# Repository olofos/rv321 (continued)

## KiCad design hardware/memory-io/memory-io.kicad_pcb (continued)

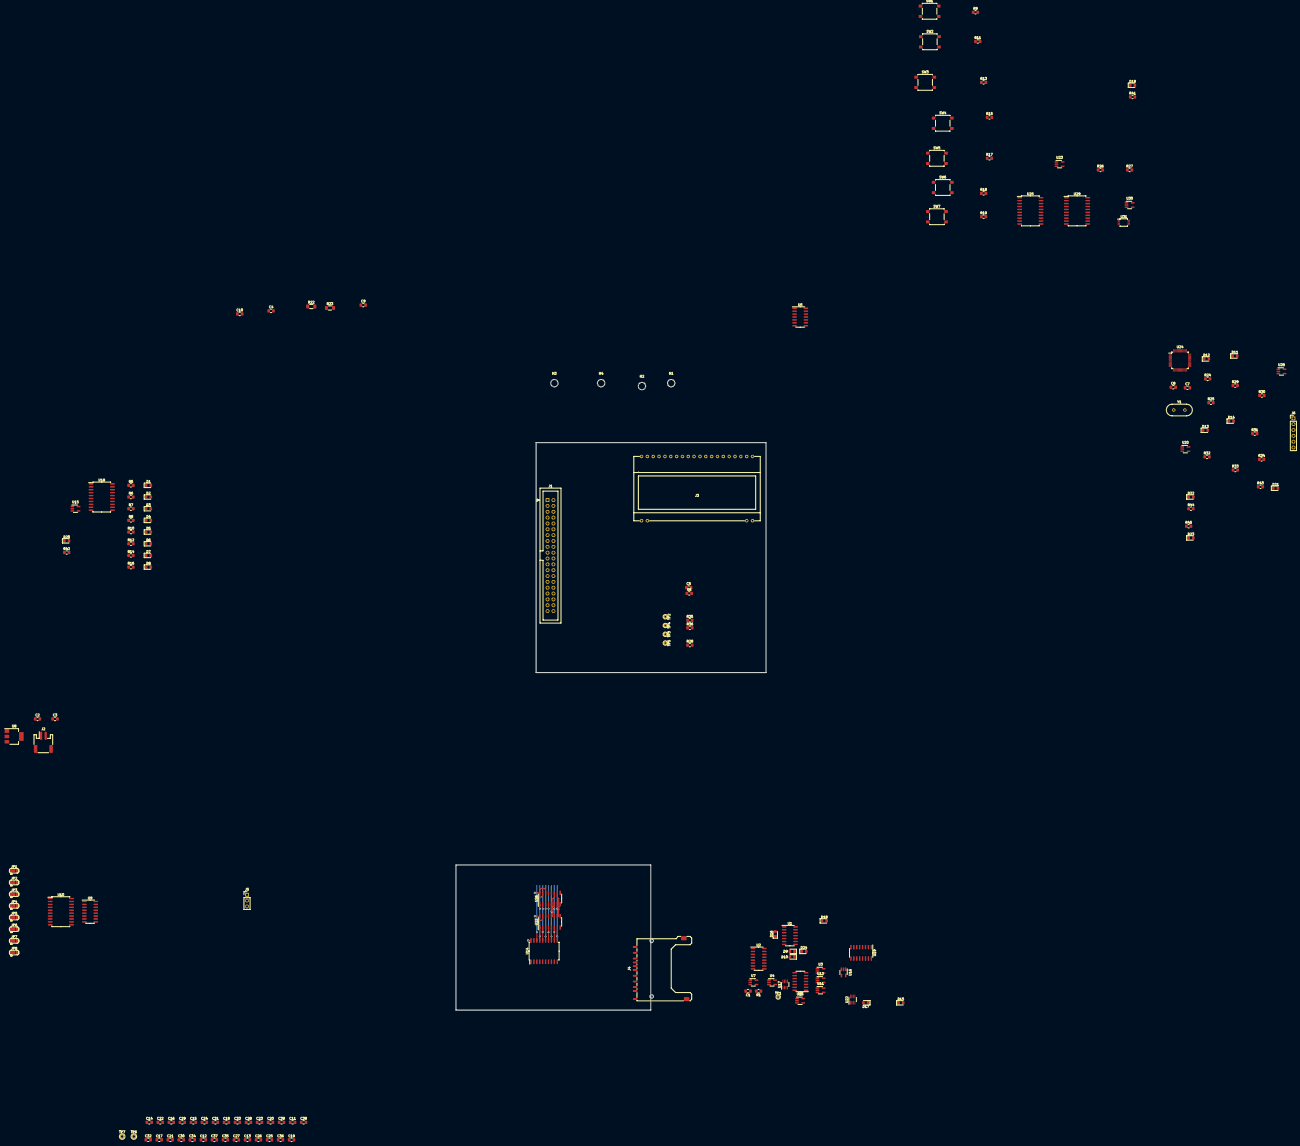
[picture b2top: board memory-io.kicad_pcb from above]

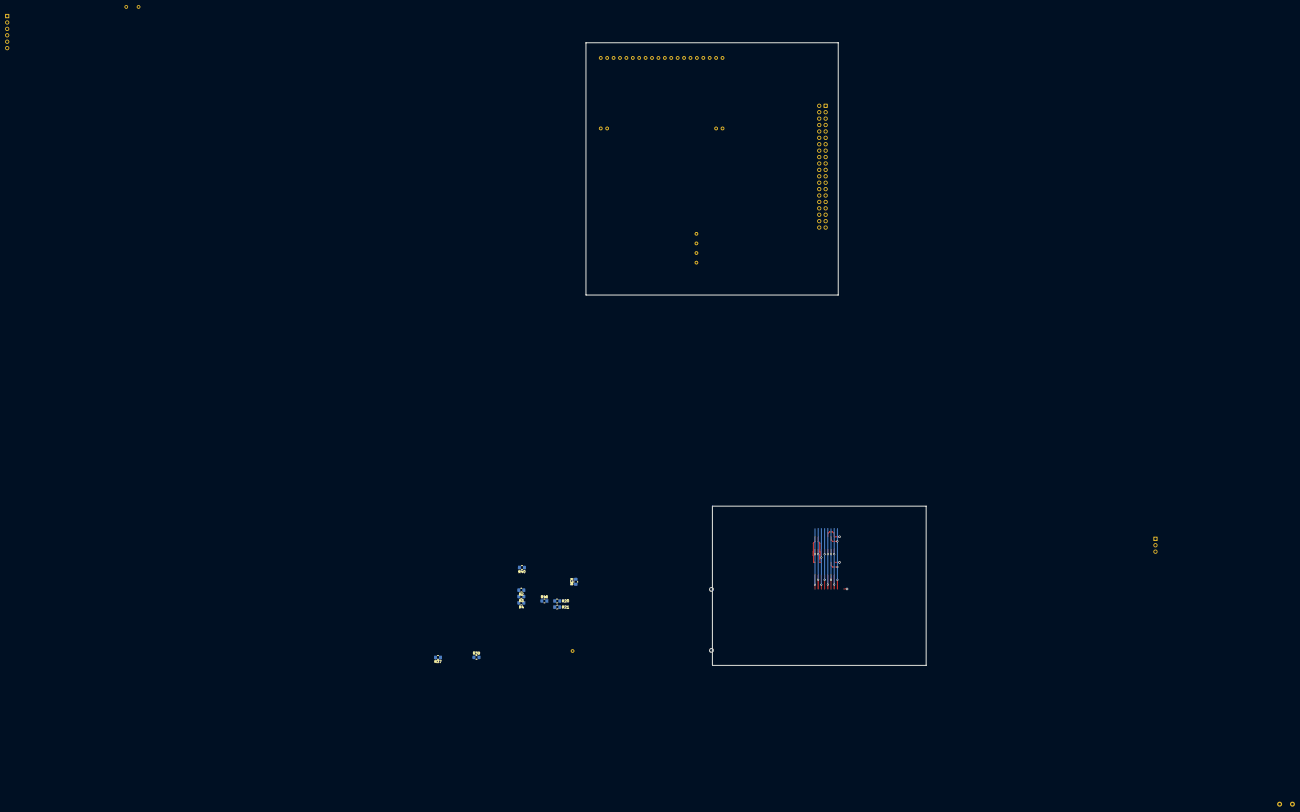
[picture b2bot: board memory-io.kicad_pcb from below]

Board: 4 copper layers, 172 parts (10 on the bottom side), 140 nets.

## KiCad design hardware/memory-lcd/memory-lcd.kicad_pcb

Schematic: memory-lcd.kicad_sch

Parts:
C1, C2: 1u; C_0805_2012Metric_Pad1.15x1.40mm_HandSolder
C3, C4, C5: 100n; C_0805_2012Metric_Pad1.15x1.40mm_HandSolder
H1, H2, H3, H4: MountingHole; MountingHole_3.2mm_M3
J1: NHD-0220FZ
J2: Conn_Mem_Ext; IDC-Header_2x20_P2.54mm_Vertical
J3: Conn_Power; JST_PH_S2B-PH-SM4-TB_1x02-1MP_P2.00mm_Horizontal
JP1, JP2, JP3, JP4, JP5, JP6: SolderJumper_3_Bridged12; SolderJumper-3_P1.3mm_Bridged2Bar12_RoundedPad1.0x1.5mm
RV1: 10k; Potentiometer_Bourns_3386P_Vertical
U1: 74HC688; SO-20_12.8x7.5mm_P1.27mm
U2: 74LVC1G08; SOT-23-5_HandSoldering
U3: MIC5504-3.3YM5; SOT-23-5_HandSoldering
U4: 74LVC1G04; SOT-23-5_HandSoldering

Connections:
/A0: J1.4 (RS), J2.2 (A0)
/A1: J2.3 (A1), U1.6 (P2)
/A2: J2.4 (A2), U1.8 (P3)
/A3: J2.5 (A3), U1.11 (P4)
/A4: J2.6 (A4), U1.13 (P5)
/A5: J2.7 (A5), U1.15 (P6)
/A6: J2.8 (A6), U1.17 (P7)
/A7: J2.9 (A7)
/A8: J2.10 (A8)
/A9: J2.11 (A9)
/A10: J2.12 (A10)
/A11: J2.13 (A11)
/A12: J2.14 (A12)
/A13: J2.15 (A13)
/A14: J2.16 (A14)
/A15: J2.17 (A15)
/A16: J2.18 (A16)
/A17: J2.19 (A17)
/A18: J2.20 (A18)
/A19: J2.21 (A19)
/A20: J2.22 (A20)
/A21: J2.23 (A21)
/A22: J2.24 (A22)
/A23: J2.25 (A23)
/A30: J2.26 (A30), U1.2 (P0)
/A31: J2.27 (A31), U1.4 (P1)
/B1: JP1.2 (C), U1.7 (R2)
/B2: JP2.2 (C), U1.9 (R3)
/B3: JP3.2 (C), U1.12 (R4)
/B4: JP4.2 (C), U1.14 (R5)
/B5: JP5.2 (C), U1.16 (R6)
/B6: JP6.2 (C), U1.18 (R7)
/D0: J1.14 (DB7), J2.32 (D0)
/D1: J1.13 (DB6), J2.33 (D1)
/D2: J1.12 (DB5), J2.34 (D2)
/D3: J1.11 (DB4), J2.35 (D3)
/D4: J1.10 (DB3), J2.36 (D4)
/D5: J1.9 (DB2), J2.37 (D5)
/D6: J1.8 (DB1), J2.38 (D6)
/D7: J1.7 (DB0), J2.39 (D7)
/LCD_E: J1.6 (E), U4.4
/V_IN: C1.2, J3.1 (VCC), U3.1 (VIN), U3.3 (EN)
/~LCD_E: U1.19 (P=R), U4.2
/~MEM_E: U1.1 (G), U2.4
/~MEM_OE: J2.30 (~MEM_OE), U2.1
/~MEM_WE: J1.5 (R/~W), J2.31 (~MEM_WE), U2.2
/~RESET: J2.28 (~RESET)
/~WAIT: J2.29 (~WAIT)
GND: C1.1, C2.1, C3.1, C4.1, C5.1, J1.1 (GND), J1.16 (K-), J2.1 (GND), J2.40 (GND), J3.2 (GND), J3.MP, JP1.1 (A), JP2.1 (A), JP3.1 (A), JP4.1 (A), JP5.1 (A), JP6.1 (A), RV1.3, U1.5 (R1), U1.10 (GND), U2.3 (GND), U3.2 (GND), U4.3 (GND)
unnamed: J1.3 (Vcontr), RV1.2
VCC: C2.2, C3.2, C4.2, C5.2, J1.2 (VCC), J1.15 (A+), JP1.3 (B), JP2.3 (B), JP3.3 (B), JP4.3 (B), JP5.3 (B), JP6.3 (B), RV1.1, U1.3 (R0), U1.20 (VCC), U2.5 (VCC), U3.5 (VOUT), U4.5 (VCC)

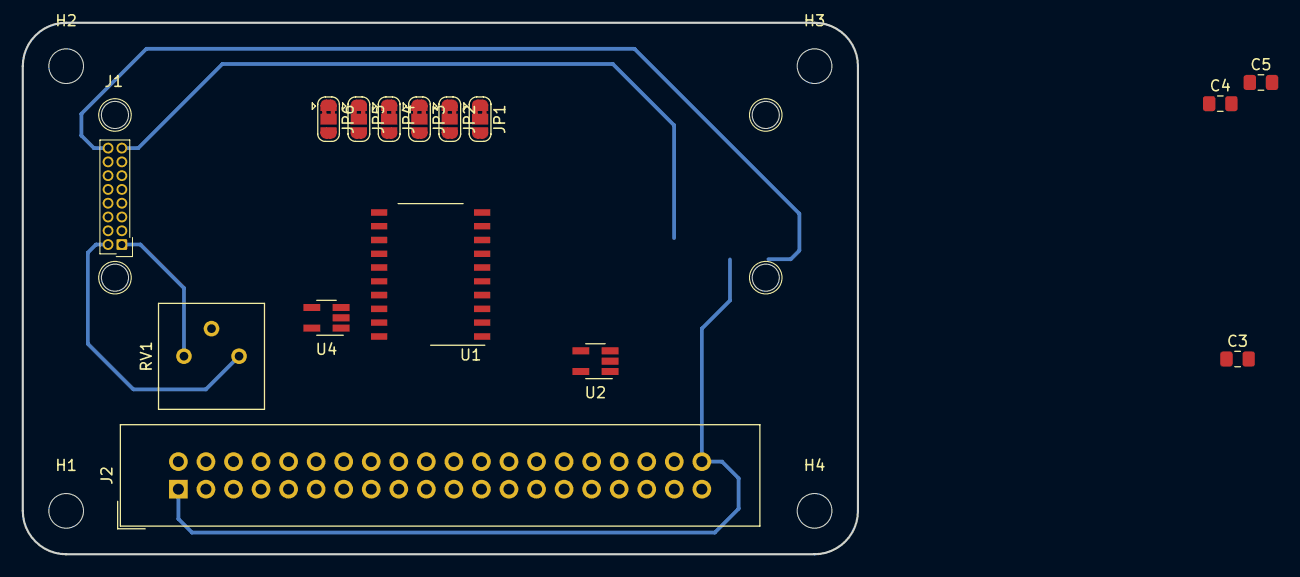
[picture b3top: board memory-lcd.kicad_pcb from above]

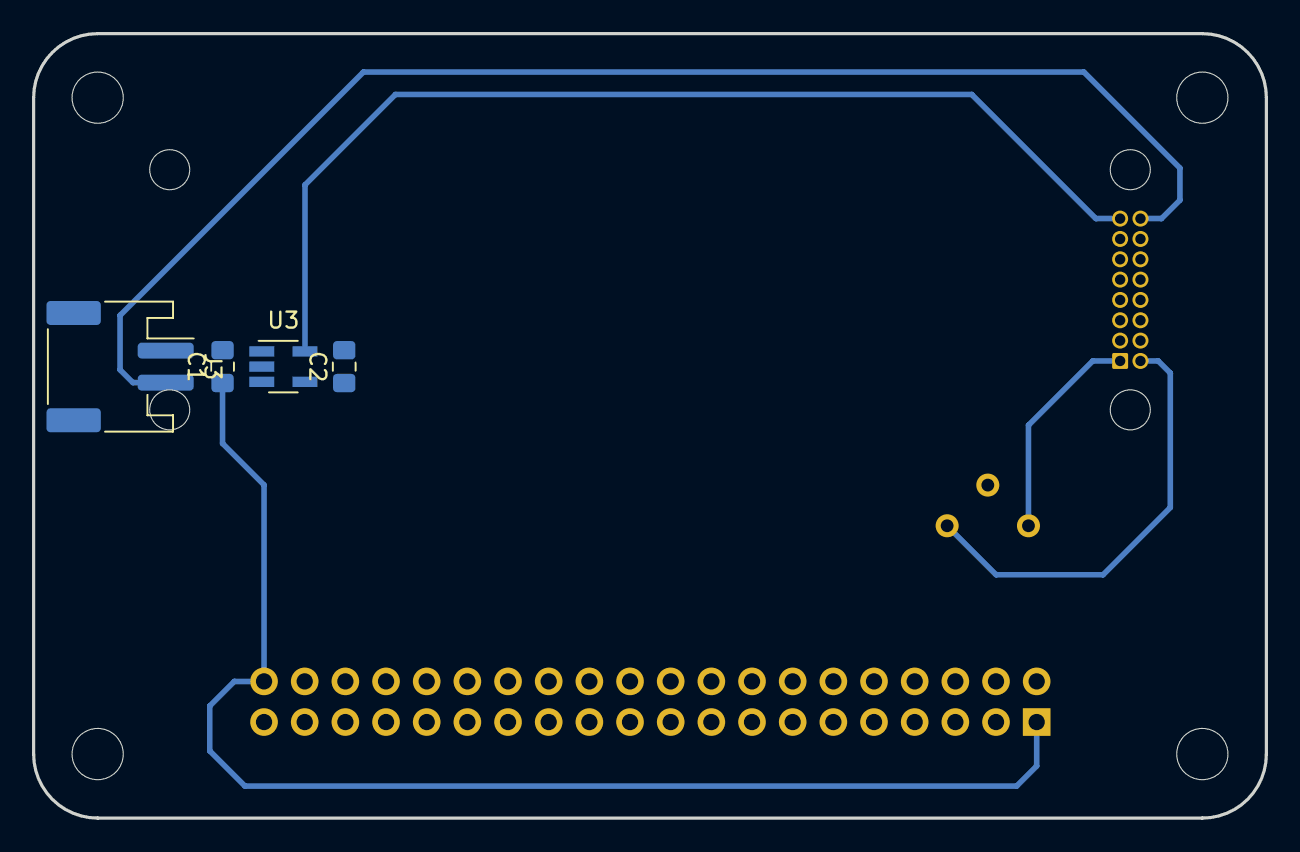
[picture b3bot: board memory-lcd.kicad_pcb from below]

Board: 2 copper layers, 77.0 x 49.0 mm, 23 parts (4 on the bottom side), 32 nets.

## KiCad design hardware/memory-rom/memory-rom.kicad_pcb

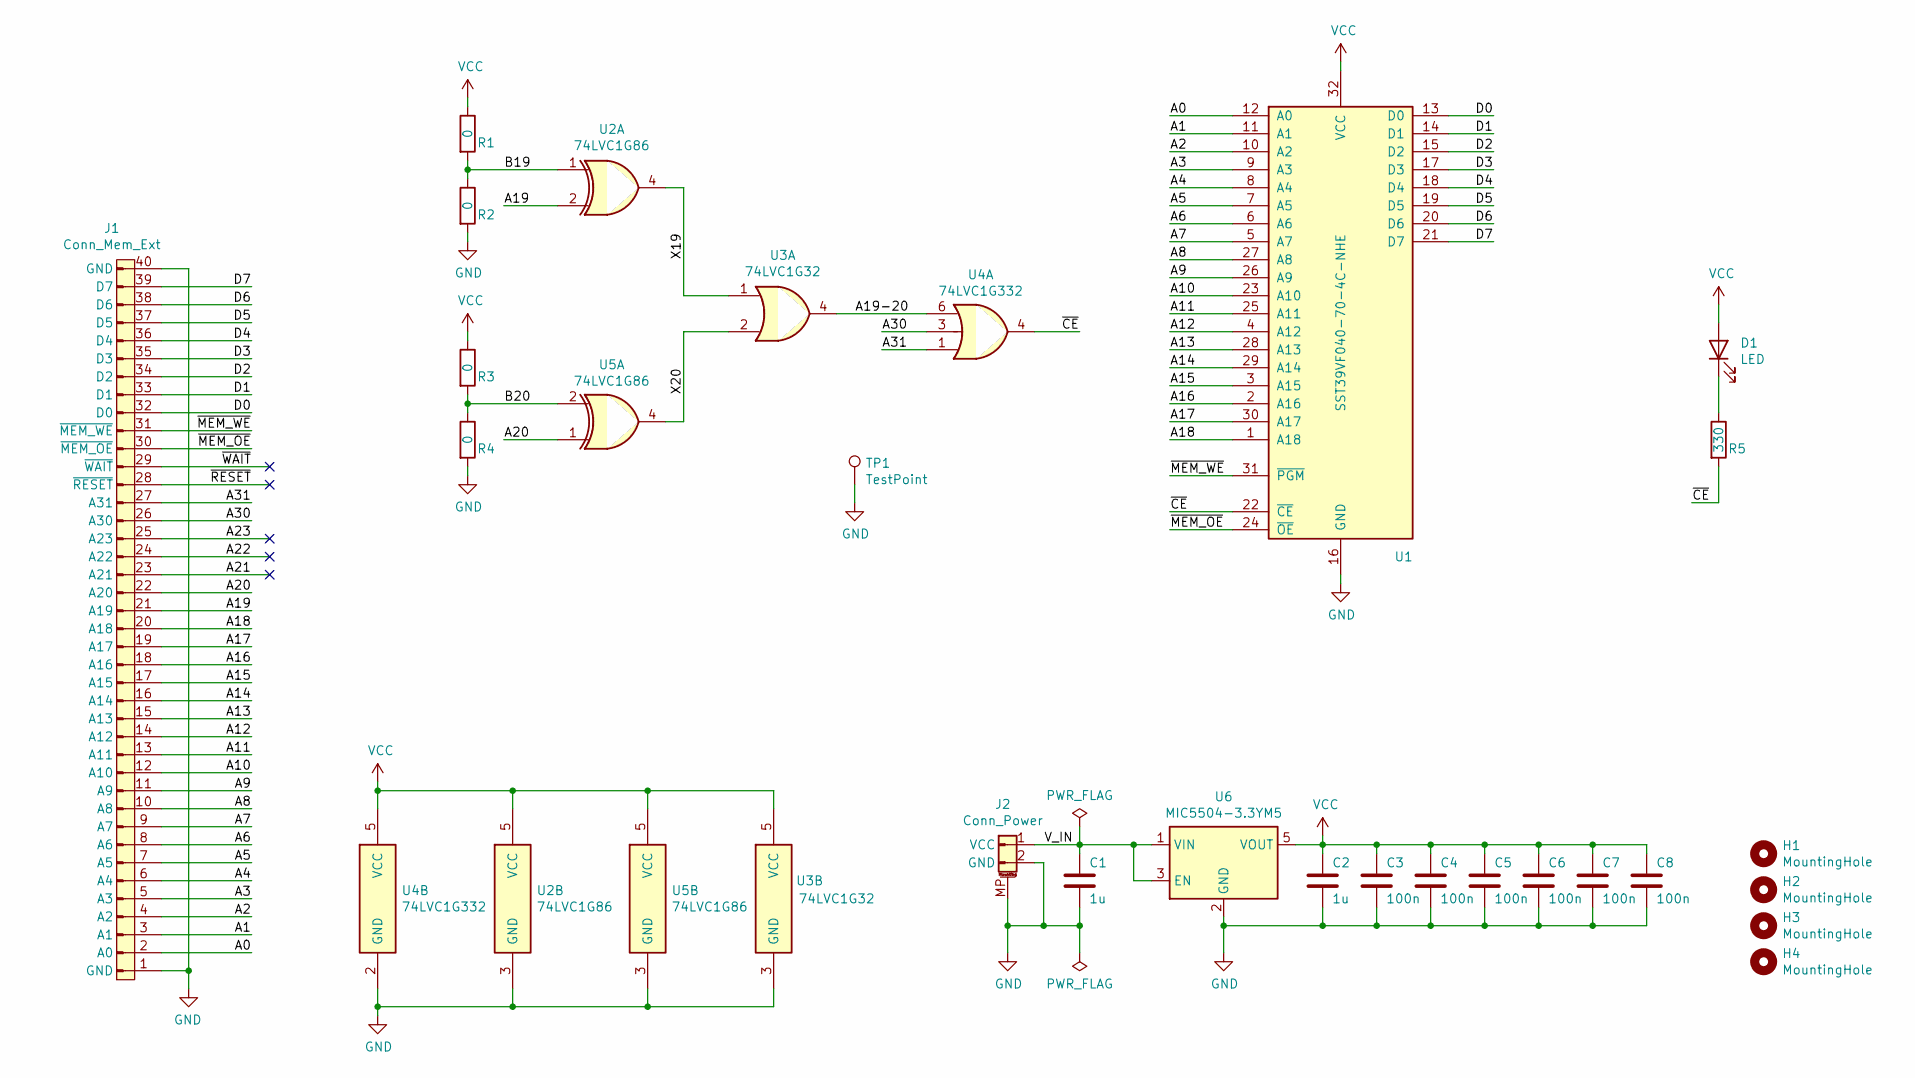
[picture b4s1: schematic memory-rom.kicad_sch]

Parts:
C1, C2: 1u; C_0805_2012Metric_Pad1.15x1.40mm_HandSolder
C3, C4, C5, C6, C7, C8: 100n; C_0805_2012Metric_Pad1.15x1.40mm_HandSolder
D1: LED; LED_0805_2012Metric_Pad1.15x1.40mm_HandSolder
H1, H2, H3, H4: MountingHole; MountingHole_3.2mm_M3
J1: Conn_Mem_Ext; IDC-Header_2x20_P2.54mm_Vertical
J2: Conn_Power; JST_PH_S2B-PH-SM4-TB_1x02-1MP_P2.00mm_Horizontal
R1, R2, R3, R4: 0; R_0805_2012Metric_Pad1.15x1.40mm_HandSolder
R5: 330; R_0805_2012Metric_Pad1.15x1.40mm_HandSolder
TP1: TestPoint; TestPoint_THTPad_D2.0mm_Drill1.0mm
U1: SST39VF040-70-4C-NHE; PLCC-32-socket-2M-8432-11B1-RK-TP
U2, U5: 74LVC1G86; SOT-23-5_HandSoldering
U3: 74LVC1G32; SOT-23-5_HandSoldering
U4: 74LVC1G332; SOT-23-6_Handsoldering
U6: MIC5504-3.3YM5; SOT-23-5_HandSoldering

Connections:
/A0: J1.2 (A0), U1.12 (A0)
/A1: J1.3 (A1), U1.11 (A1)
/A2: J1.4 (A2), U1.10 (A2)
/A3: J1.5 (A3), U1.9 (A3)
/A4: J1.6 (A4), U1.8 (A4)
/A5: J1.7 (A5), U1.7 (A5)
/A6: J1.8 (A6), U1.6 (A6)
/A7: J1.9 (A7), U1.5 (A7)
/A8: J1.10 (A8), U1.27 (A8)
/A9: J1.11 (A9), U1.26 (A9)
/A10: J1.12 (A10), U1.23 (A10)
/A11: J1.13 (A11), U1.25 (A11)
/A12: J1.14 (A12), U1.4 (A12)
/A13: J1.15 (A13), U1.28 (A13)
/A14: J1.16 (A14), U1.29 (A14)
/A15: J1.17 (A15), U1.3 (A15)
/A16: J1.18 (A16), U1.2 (A16)
/A17: J1.19 (A17), U1.30 (A17)
/A18: J1.20 (A18), U1.1 (A18)
/A19: J1.21 (A19), U2.2
/A19-20: U3.4, U4.6
/A20: J1.22 (A20), U5.1
/A21: J1.23 (A21)
/A22: J1.24 (A22)
/A23: J1.25 (A23)
/A30: J1.26 (A30), U4.3
/A31: J1.27 (A31), U4.1
/B19: R1.2, R2.1, U2.1
/B20: R3.2, R4.1, U5.2
/D0: J1.32 (D0), U1.13 (D0)
/D1: J1.33 (D1), U1.14 (D1)
/D2: J1.34 (D2), U1.15 (D2)
/D3: J1.35 (D3), U1.17 (D3)
/D4: J1.36 (D4), U1.18 (D4)
/D5: J1.37 (D5), U1.19 (D5)
/D6: J1.38 (D6), U1.20 (D6)
/D7: J1.39 (D7), U1.21 (D7)
/V_IN: C1.2, J2.1 (VCC), U6.1 (VIN), U6.3 (EN)
/X19: U2.4, U3.1
/X20: U3.2, U5.4
/~CE: R5.2, U1.22 (~CE), U4.4
/~MEM_OE: J1.30 (~MEM_OE), U1.24 (~OE)
/~MEM_WE: J1.31 (~MEM_WE), U1.31 (~PGM)
/~RESET: J1.28 (~RESET)
/~WAIT: J1.29 (~WAIT)
GND: C1.1, C2.1, C3.1, C4.1, C5.1, C6.1, C7.1, C8.1, J1.1 (GND), J1.40 (GND), J2.2 (GND), J2.MP, R2.2, R4.2, TP1.1, U1.16 (GND), U2.3 (GND), U3.3 (GND), U4.2 (GND), U5.3 (GND), U6.2 (GND)
unnamed: D1.1 (K), R5.1
VCC: C2.2, C3.2, C4.2, C5.2, C6.2, C7.2, C8.2, D1.2 (A), R1.1, R3.1, U1.32 (VCC), U2.5 (VCC), U3.5 (VCC), U4.5 (VCC), U5.5 (VCC), U6.5 (VOUT)

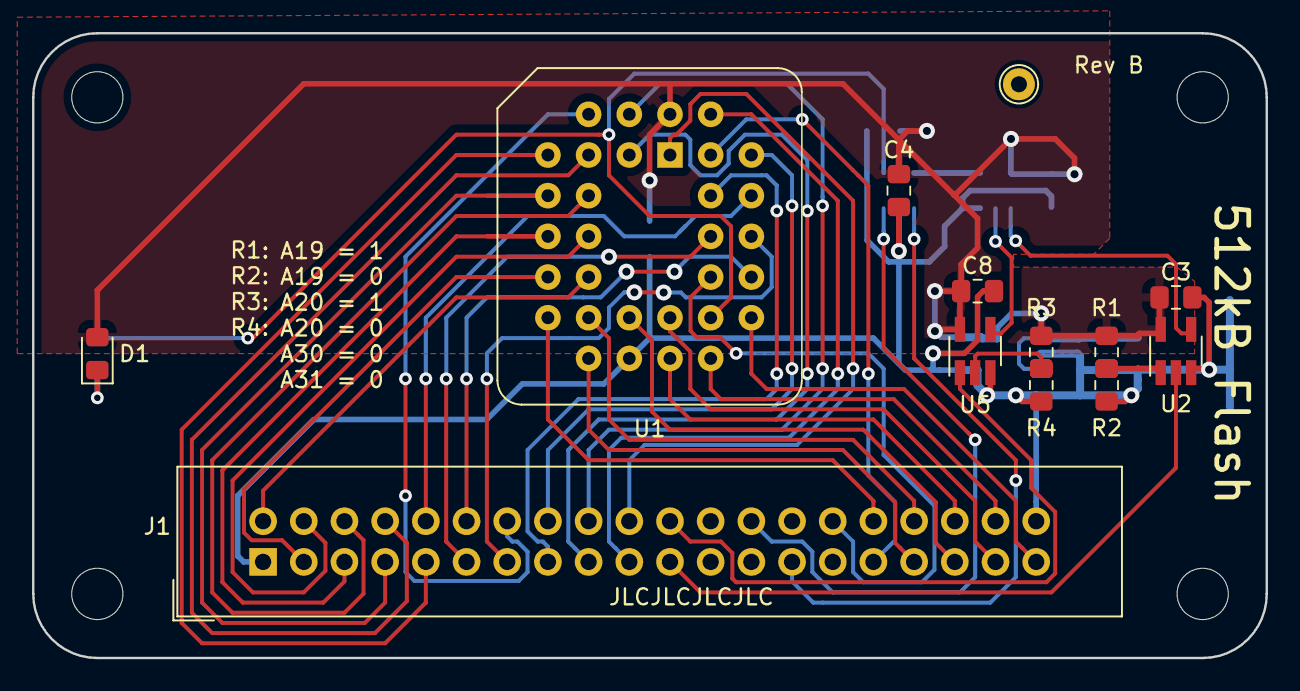
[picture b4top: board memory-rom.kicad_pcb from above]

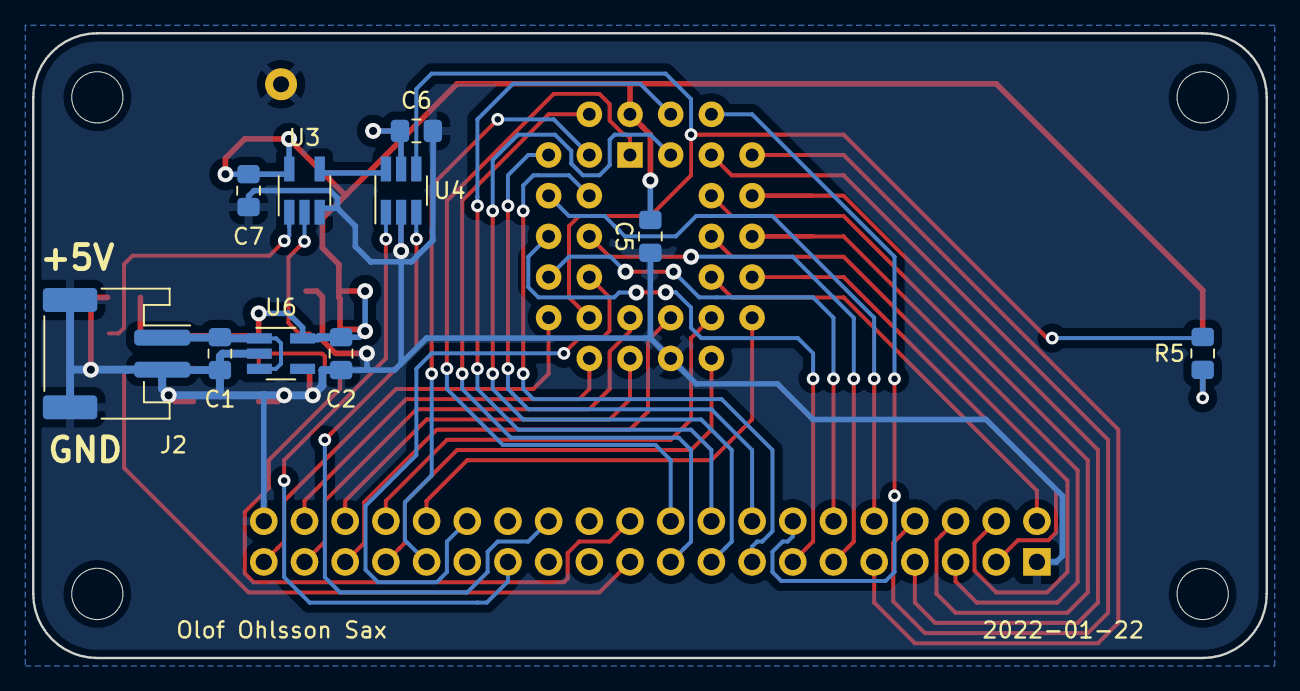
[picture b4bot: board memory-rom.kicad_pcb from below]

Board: 2 copper layers, 77.0 x 39.0 mm, 27 parts (10 on the bottom side), 43 nets.

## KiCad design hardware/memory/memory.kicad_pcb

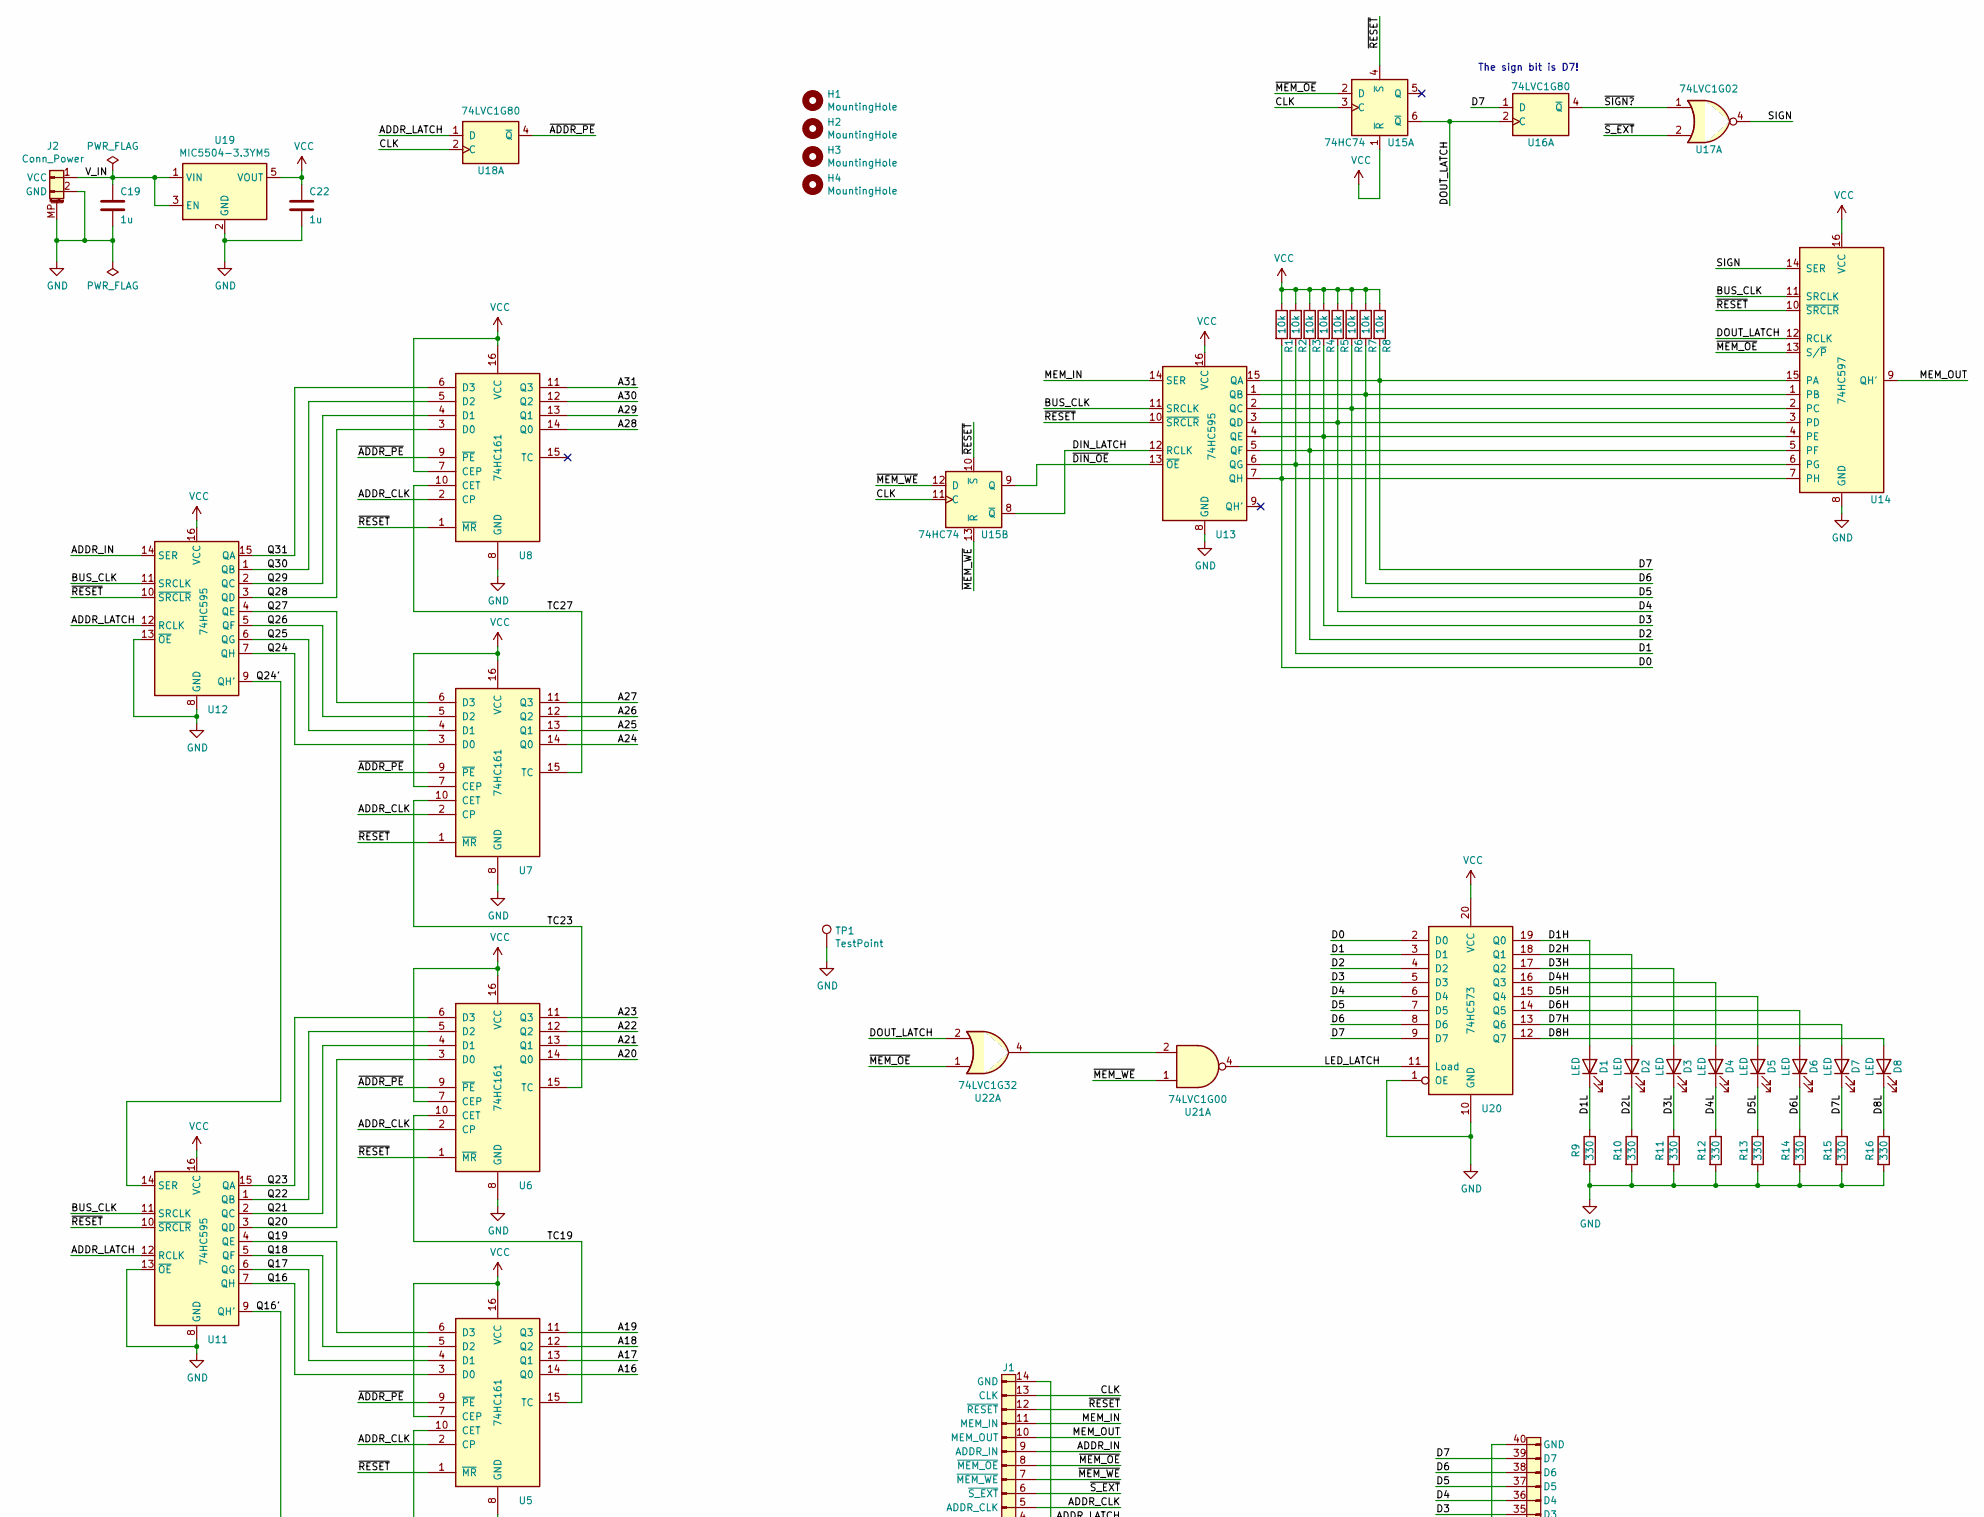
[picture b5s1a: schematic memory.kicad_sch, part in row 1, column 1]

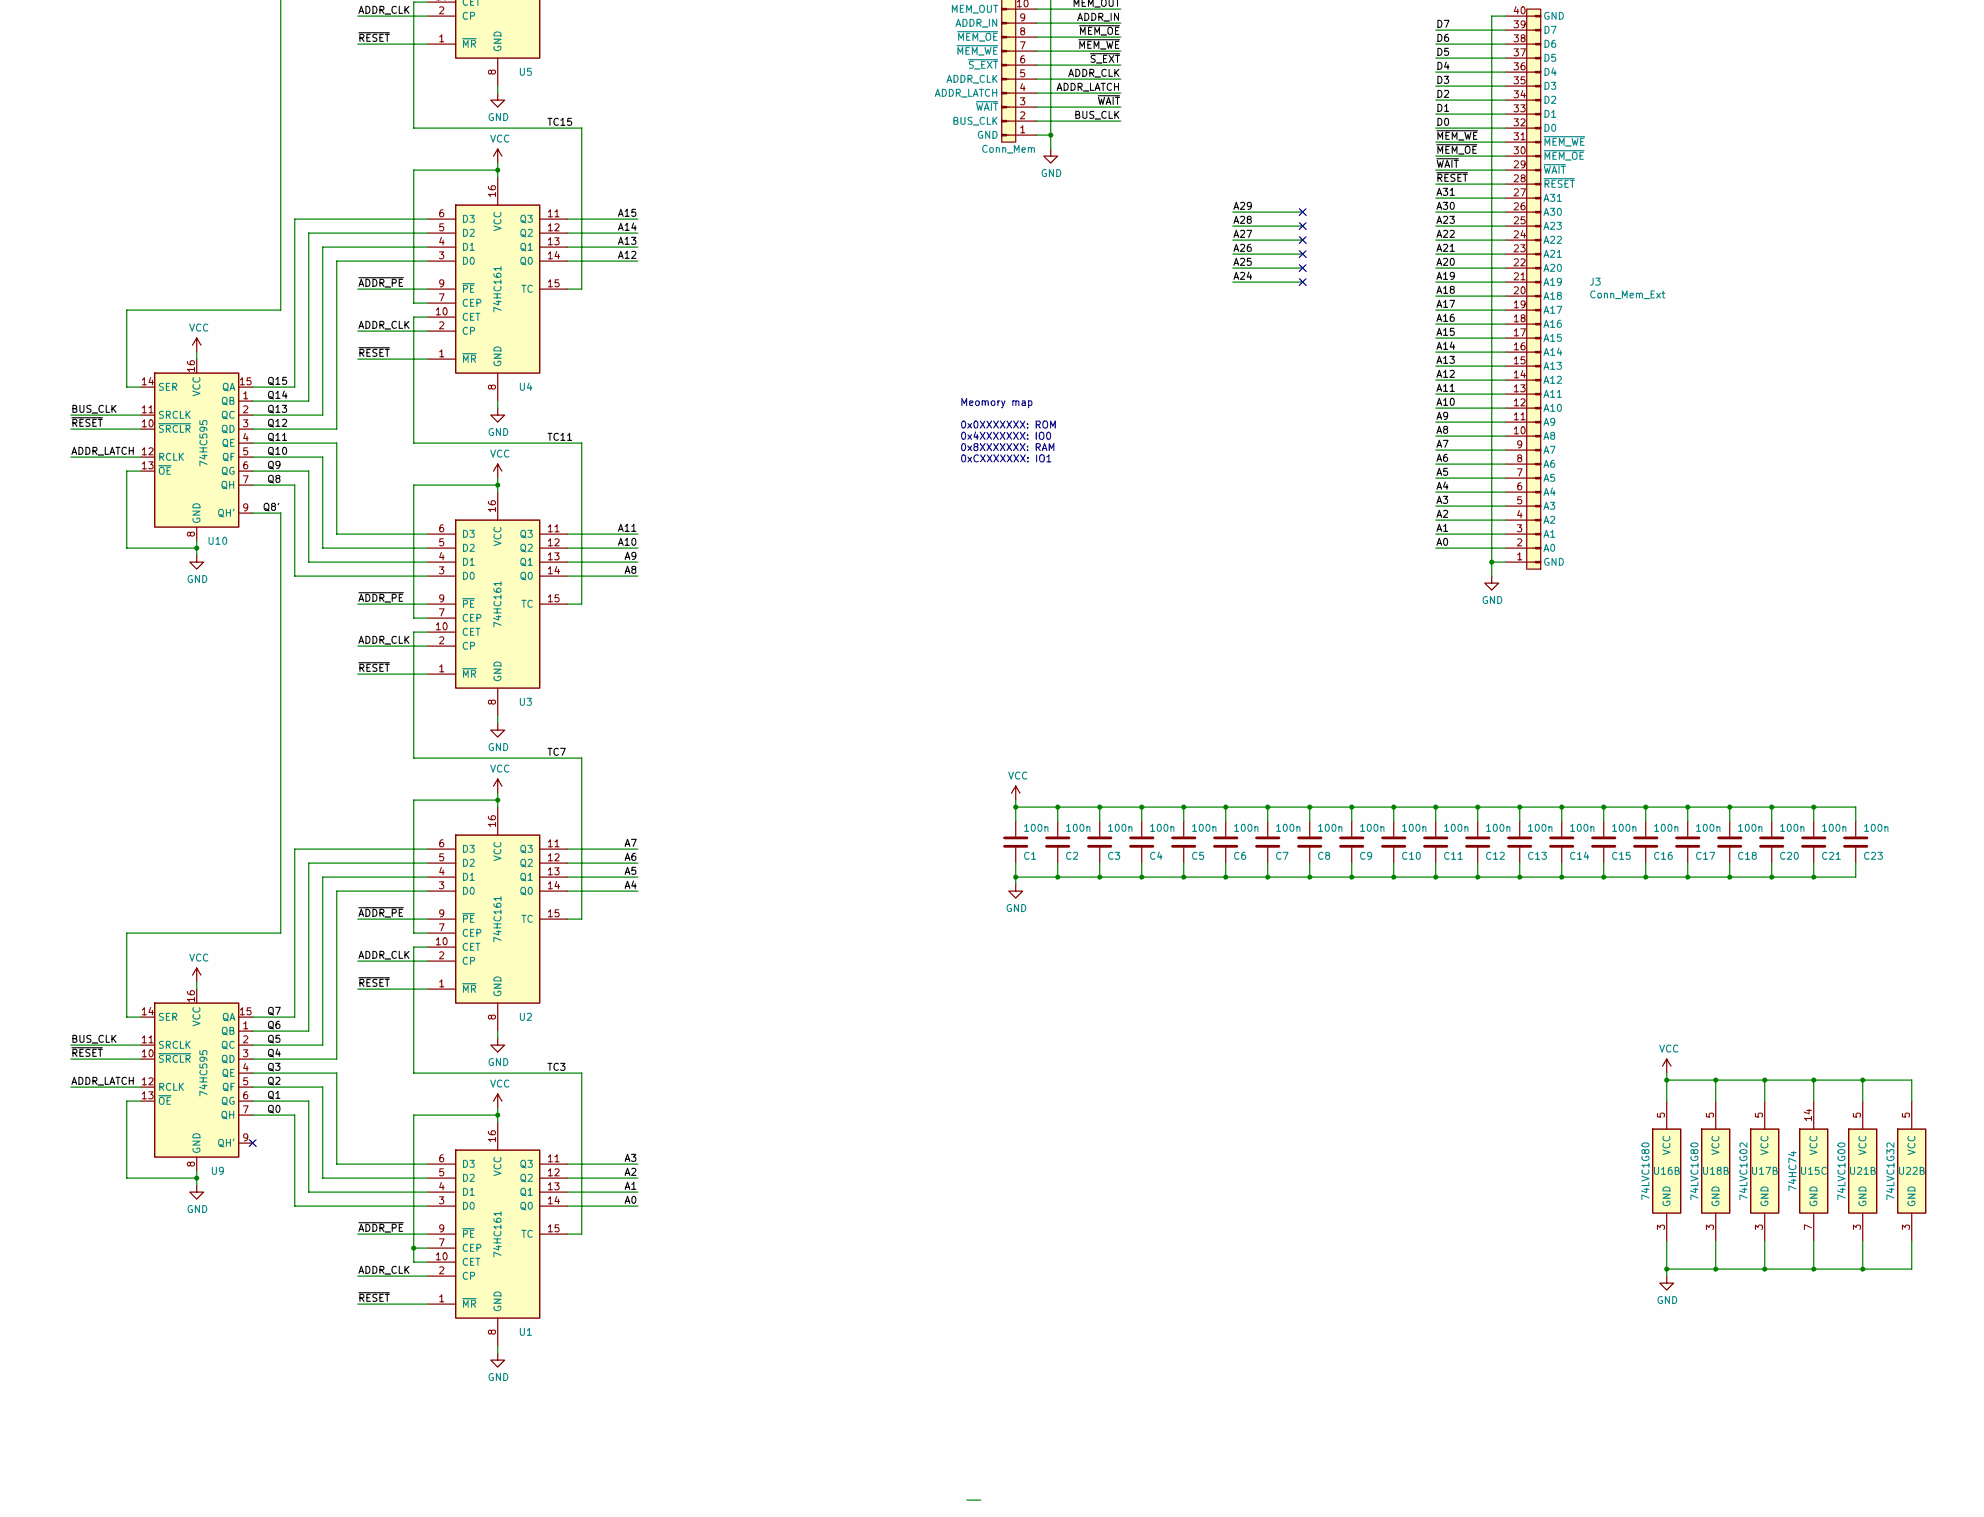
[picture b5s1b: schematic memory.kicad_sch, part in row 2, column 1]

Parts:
C1, C2, C3, C4, C5, C6, C7, C8, C9, C10, C11, C12, C13, C14, C15, C16, C17, C18, C20, C21: 100n; C_0805_2012Metric_Pad1.15x1.40mm_HandSolder
C19, C22: 1u; C_0805_2012Metric_Pad1.15x1.40mm_HandSolder
C23: 100n; C_0805_2012Metric_Pad1.18x1.45mm_HandSolder
D1, D2, D3, D4, D5, D6, D7, D8: LED; LED_0805_2012Metric_Pad1.15x1.40mm_HandSolder
H1, H2, H3, H4: MountingHole; MountingHole_3.2mm_M3
J1: Conn_Mem; IDC-Header_2x07_P2.54mm_Vertical
J2: Conn_Power; JST_PH_S2B-PH-SM4-TB_1x02-1MP_P2.00mm_Horizontal
J3: Conn_Mem_Ext; IDC-Header_2x20_P2.54mm_Vertical
R1, R2, R3, R4, R5, R6, R7, R8: 10k; R_0805_2012Metric_Pad1.15x1.40mm_HandSolder
R9, R10, R11, R12, R13, R14, R15, R16: 330; R_0805_2012Metric_Pad1.15x1.40mm_HandSolder
TP1: TestPoint; TestPoint_THTPad_D2.0mm_Drill1.0mm
U1, U2, U3, U4, U5, U6, U7, U8: 74HC161; SOIC-16_3.9x9.9mm_P1.27mm
U9, U10, U11, U12, U13: 74HC595; SOIC-16_3.9x9.9mm_P1.27mm
U14: 74HC597; SOIC-16_3.9x9.9mm_P1.27mm
U15: 74HC74; SOIC-14_3.9x8.7mm_P1.27mm
U16, U18: 74LVC1G80; SOT-23-5_HandSoldering
U17: 74LVC1G02; SOT-23-5_HandSoldering
U19: MIC5504-3.3YM5; SOT-23-5_HandSoldering
U20: 74HC573; TSSOP-20_4.4x6.5mm_P0.65mm
U21: 74LVC1G00; SOT-23-5_HandSoldering
U22: 74LVC1G32; SOT-23-5_HandSoldering

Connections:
/A0: J3.2 (A0), U1.14 (Q0)
/A1: J3.3 (A1), U1.13 (Q1)
/A2: J3.4 (A2), U1.12 (Q2)
/A3: J3.5 (A3), U1.11 (Q3)
/A4: J3.6 (A4), U2.14 (Q0)
/A5: J3.7 (A5), U2.13 (Q1)
/A6: J3.8 (A6), U2.12 (Q2)
/A7: J3.9 (A7), U2.11 (Q3)
/A8: J3.10 (A8), U3.14 (Q0)
/A9: J3.11 (A9), U3.13 (Q1)
/A10: J3.12 (A10), U3.12 (Q2)
/A11: J3.13 (A11), U3.11 (Q3)
/A12: J3.14 (A12), U4.14 (Q0)
/A13: J3.15 (A13), U4.13 (Q1)
/A14: J3.16 (A14), U4.12 (Q2)
/A15: J3.17 (A15), U4.11 (Q3)
/A16: J3.18 (A16), U5.14 (Q0)
/A17: J3.19 (A17), U5.13 (Q1)
/A18: J3.20 (A18), U5.12 (Q2)
/A19: J3.21 (A19), U5.11 (Q3)
/A20: J3.22 (A20), U6.14 (Q0)
/A21: J3.23 (A21), U6.13 (Q1)
/A22: J3.24 (A22), U6.12 (Q2)
/A23: J3.25 (A23), U6.11 (Q3)
/A24: U7.14 (Q0)
/A25: U7.13 (Q1)
/A26: U7.12 (Q2)
/A27: U7.11 (Q3)
/A28: U8.14 (Q0)
/A29: U8.13 (Q1)
/A30: J3.26 (A30), U8.12 (Q2)
/A31: J3.27 (A31), U8.11 (Q3)
/ADDR_CLK: J1.5 (ADDR_CLK), U1.2 (CP), U2.2 (CP), U3.2 (CP), U4.2 (CP), U5.2 (CP), U6.2 (CP), U7.2 (CP), U8.2 (CP)
/ADDR_IN: J1.9 (ADDR_IN), U12.14 (SER)
/ADDR_LATCH: J1.4 (ADDR_LATCH), U9.12 (RCLK), U10.12 (RCLK), U11.12 (RCLK), U12.12 (RCLK), U18.1 (D)
/BUS_CLK: J1.2 (BUS_CLK), U9.11 (SRCLK), U10.11 (SRCLK), U11.11 (SRCLK), U12.11 (SRCLK), U13.11 (SRCLK), U14.11 (SRCLK)
/CLK: J1.13 (CLK), U15.3 (C), U15.11 (C), U18.2 (C)
/D0: J3.32 (D0), R1.2, U13.7 (QH), U14.7 (PH), U20.2 (D0)
/D1: J3.33 (D1), R2.2, U13.6 (QG), U14.6 (PG), U20.3 (D1)
/D1H: D1.2 (A), U20.19 (Q0)
/D1L: D1.1 (K), R9.1
/D2: J3.34 (D2), R3.2, U13.5 (QF), U14.5 (PF), U20.4 (D2)
/D2H: D2.2 (A), U20.18 (Q1)
/D2L: D2.1 (K), R10.1
/D3: J3.35 (D3), R4.2, U13.4 (QE), U14.4 (PE), U20.5 (D3)
/D3H: D3.2 (A), U20.17 (Q2)
/D3L: D3.1 (K), R11.1
/D4: J3.36 (D4), R5.2, U13.3 (QD), U14.3 (PD), U20.6 (D4)
/D4H: D4.2 (A), U20.16 (Q3)
/D4L: D4.1 (K), R12.1
/D5: J3.37 (D5), R6.2, U13.2 (QC), U14.2 (PC), U20.7 (D5)
/D5H: D5.2 (A), U20.15 (Q4)
/D5L: D5.1 (K), R13.1
/D6: J3.38 (D6), R7.2, U13.1 (QB), U14.1 (PB), U20.8 (D6)
/D6H: D6.2 (A), U20.14 (Q5)
/D6L: D6.1 (K), R14.1
/D7: J3.39 (D7), R8.2, U13.15 (QA), U14.15 (PA), U16.1 (D), U20.9 (D7)
/D7H: D7.2 (A), U20.13 (Q6)
/D7L: D7.1 (K), R15.1
/D8H: D8.2 (A), U20.12 (Q7)
/D8L: D8.1 (K), R16.1
/DIN_LATCH: U13.12 (RCLK), U15.8 (~Q)
/DOUT_LATCH: U14.12 (RCLK), U15.6 (~Q), U16.2 (C), U22.2
/LED_LATCH: U20.11 (Load), U21.4
/MEM_IN: J1.11 (MEM_IN), U13.14 (SER)
/MEM_OUT: J1.10 (MEM_OUT), U14.9 (QH')
/Q0: U1.3 (D0), U9.7 (QH)
/Q1: U1.4 (D1), U9.6 (QG)
/Q2: U1.5 (D2), U9.5 (QF)
/Q3: U1.6 (D3), U9.4 (QE)
/Q4: U2.3 (D0), U9.3 (QD)
/Q5: U2.4 (D1), U9.2 (QC)
/Q6: U2.5 (D2), U9.1 (QB)
/Q7: U2.6 (D3), U9.15 (QA)
/Q8: U3.3 (D0), U10.7 (QH)
/Q8': U9.14 (SER), U10.9 (QH')
/Q9: U3.4 (D1), U10.6 (QG)
/Q10: U3.5 (D2), U10.5 (QF)
/Q11: U3.6 (D3), U10.4 (QE)
/Q12: U4.3 (D0), U10.3 (QD)
/Q13: U4.4 (D1), U10.2 (QC)
/Q14: U4.5 (D2), U10.1 (QB)
/Q15: U4.6 (D3), U10.15 (QA)
/Q16: U5.3 (D0), U11.7 (QH)
/Q16': U10.14 (SER), U11.9 (QH')
/Q17: U5.4 (D1), U11.6 (QG)
/Q18: U5.5 (D2), U11.5 (QF)
/Q19: U5.6 (D3), U11.4 (QE)
/Q20: U6.3 (D0), U11.3 (QD)
/Q21: U6.4 (D1), U11.2 (QC)
/Q22: U6.5 (D2), U11.1 (QB)
/Q23: U6.6 (D3), U11.15 (QA)
/Q24: U7.3 (D0), U12.7 (QH)
/Q24': U11.14 (SER), U12.9 (QH')
/Q25: U7.4 (D1), U12.6 (QG)
/Q26: U7.5 (D2), U12.5 (QF)
/Q27: U7.6 (D3), U12.4 (QE)
/Q28: U8.3 (D0), U12.3 (QD)
/Q29: U8.4 (D1), U12.2 (QC)
/Q30: U8.5 (D2), U12.1 (QB)
/Q31: U8.6 (D3), U12.15 (QA)
/SIGN: U14.14 (SER), U17.4
/TC3: U1.15 (TC), U2.10 (CET)
/TC7: U2.15 (TC), U3.10 (CET)
/TC11: U3.15 (TC), U4.10 (CET)
/TC15: U4.15 (TC), U5.10 (CET)
/TC19: U5.15 (TC), U6.10 (CET)
/TC23: U6.15 (TC), U7.10 (CET)
/TC27: U7.15 (TC), U8.10 (CET)
/V_IN: C19.2, J2.1 (VCC), U19.1 (VIN), U19.3 (EN)
/~ADDR_PE: U1.9 (~PE), U2.9 (~PE), U3.9 (~PE), U4.9 (~PE), U5.9 (~PE), U6.9 (~PE), U7.9 (~PE), U8.9 (~PE), U18.4 (~Q)
/~DIN_OE: U13.13 (~OE), U15.9 (Q)
/~MEM_OE: J1.8 (~MEM_OE), J3.30 (~MEM_OE), U14.13 (S/~P), U15.2 (D), U22.1
/~MEM_WE: J1.7 (~MEM_WE), J3.31 (~MEM_WE), U15.12 (D), U15.13 (~R), U21.1
/~RESET: J1.12 (~RESET), J3.28 (~RESET), U1.1 (~MR), U2.1 (~MR), U3.1 (~MR), U4.1 (~MR), U5.1 (~MR), U6.1 (~MR), U7.1 (~MR), U8.1 (~MR), U9.10 (~SRCLR), U10.10 (~SRCLR), U11.10 (~SRCLR), U12.10 (~SRCLR), U13.10 (~SRCLR), U14.10 (~SRCLR), U15.4 (~S), U15.10 (~S)
/~SIGN?: U16.4 (~Q), U17.1
/~S_EXT: J1.6 (~S_EXT), U17.2
/~WAIT: J1.3 (~WAIT), J3.29 (~WAIT)
GND: C1.2, C2.2, C3.2, C4.2, C5.2, C6.2, C7.2, C8.2, C9.2, C10.2, C11.2, C12.2, C13.2, C14.2, C15.2, C16.2, C17.2, C18.2, C19.1, C20.2, C21.2, C22.1, C23.2, J1.1 (GND), J1.14 (GND), J2.2 (GND), J2.MP, J3.1 (GND), J3.40 (GND), R9.2, R10.2, R11.2, R12.2, R13.2, R14.2, R15.2, R16.2, TP1.1, U1.8 (GND), U2.8 (GND), U3.8 (GND), U4.8 (GND), U5.8 (GND), U6.8 (GND), U7.8 (GND), U8.8 (GND), U9.8 (GND), U9.13 (~OE), U10.8 (GND), U10.13 (~OE), U11.8 (GND), U11.13 (~OE), U12.8 (GND), U12.13 (~OE), U13.8 (GND), U14.8 (GND), U15.7 (GND), U16.3 (GND), U17.3 (GND), U18.3 (GND), U19.2 (GND), U20.1 (OE), U20.10 (GND), U21.3 (GND), U22.3 (GND)
unnamed: U21.2, U22.4
VCC: C1.1, C2.1, C3.1, C4.1, C5.1, C6.1, C7.1, C8.1, C9.1, C10.1, C11.1, C12.1, C13.1, C14.1, C15.1, C16.1, C17.1, C18.1, C20.1, C21.1, C22.2, C23.1, R1.1, R2.1, R3.1, R4.1, R5.1, R6.1, R7.1, R8.1, U1.7 (CEP), U1.10 (CET), U1.16 (VCC), U2.7 (CEP), U2.16 (VCC), U3.7 (CEP), U3.16 (VCC), U4.7 (CEP), U4.16 (VCC), U5.7 (CEP), U5.16 (VCC), U6.7 (CEP), U6.16 (VCC), U7.7 (CEP), U7.16 (VCC), U8.7 (CEP), U8.16 (VCC), U9.16 (VCC), U10.16 (VCC), U11.16 (VCC), U12.16 (VCC), U13.16 (VCC), U14.16 (VCC), U15.1 (~R), U15.14 (VCC), U16.5 (VCC), U17.5 (VCC), U18.5 (VCC), U19.5 (VOUT), U20.20 (VCC), U21.5 (VCC), U22.5 (VCC)

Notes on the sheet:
The sign bit is D7!
Meomory map 0x0XXXXXXX: ROM 0x4XXXXXXX: IO0 0x8XXXXXXX: RAM 0xCXXXXXXX: IO1
